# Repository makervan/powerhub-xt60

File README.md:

# Powerhub XT60

A distribution board for up to 6 XT60 connectors (male or female), with optional power LED as well as screw terminals.

## License
* Licensed under Creative Commons Attribution-ShareAlike 4.0 Unported License (CC BY-SA 4.0)
* Based on the [XT60 Board](https://github.com/jesseaster/xt60board)
* Credit for the XT60.kicad_mod goes to https://pappkopp.com/?p=222

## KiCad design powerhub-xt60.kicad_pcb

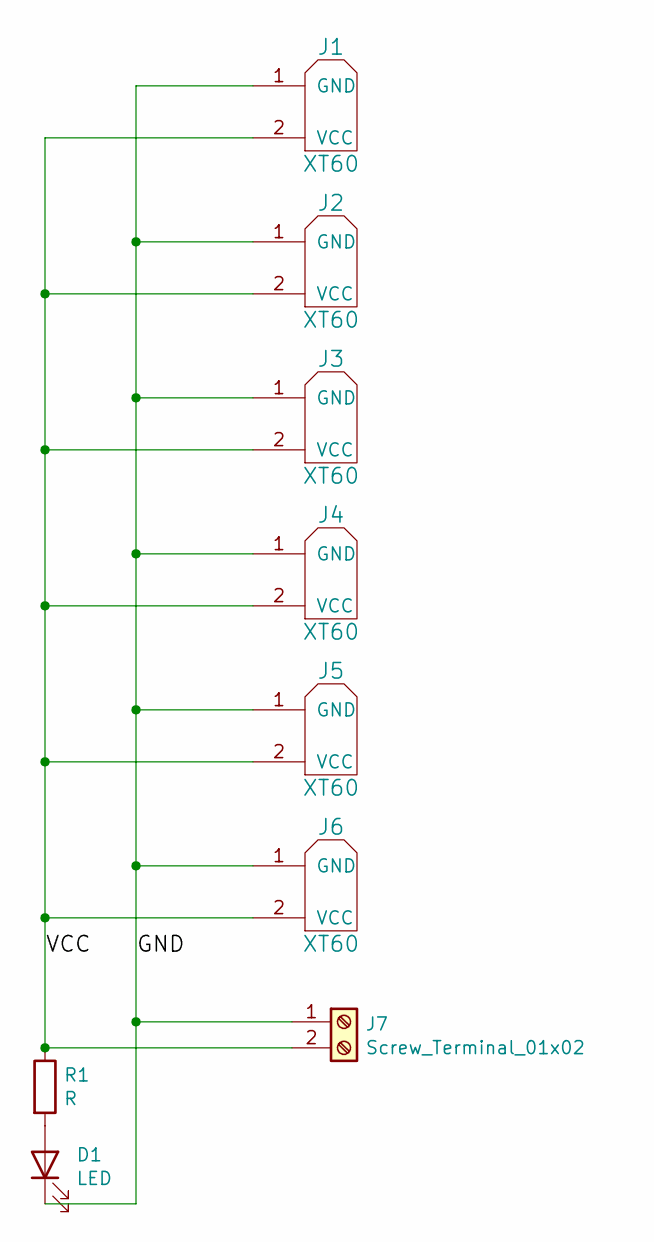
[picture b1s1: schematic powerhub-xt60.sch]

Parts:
D1: LED; LED_D3.0mm
J1, J2, J3, J4, J5, J6: XT60
J7: Screw_Terminal_01x02; TerminalBlock_RND_205-00232_1x02_P5.08mm_Horizontal
R1: R; R_Axial_DIN0204_L3.6mm_D1.6mm_P7.62mm_Horizontal

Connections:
/GND: D1.1 (K), J1.1 (GND), J2.1 (GND), J3.1 (GND), J4.1 (GND), J5.1 (GND), J6.1 (GND), J7.1
/VCC: J1.2 (VCC), J2.2 (VCC), J3.2 (VCC), J4.2 (VCC), J5.2 (VCC), J6.2 (VCC), J7.2, R1.1
unnamed: D1.2 (A), R1.2

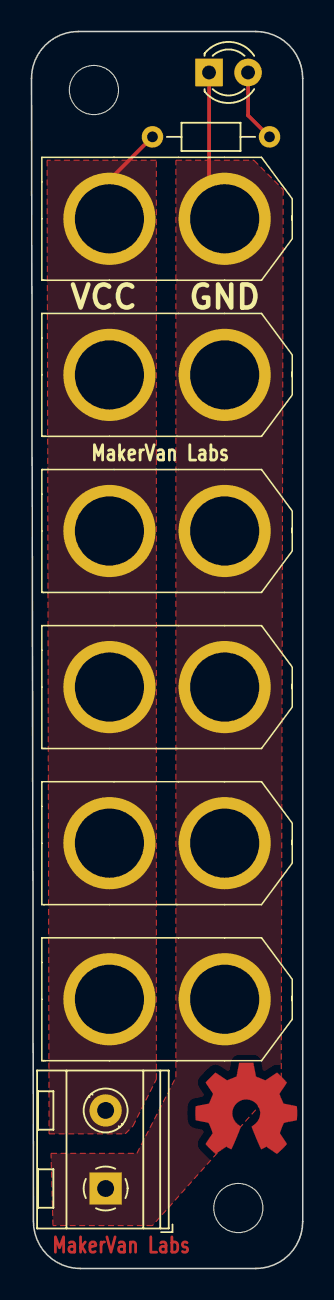
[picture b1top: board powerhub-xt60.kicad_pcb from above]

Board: 2 copper layers, 17.7 x 80.5 mm, 9 parts (0 on the bottom side), 3 nets.

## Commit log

2021-03-02 First commit of powerhub-xt60
2021-03-03 License
